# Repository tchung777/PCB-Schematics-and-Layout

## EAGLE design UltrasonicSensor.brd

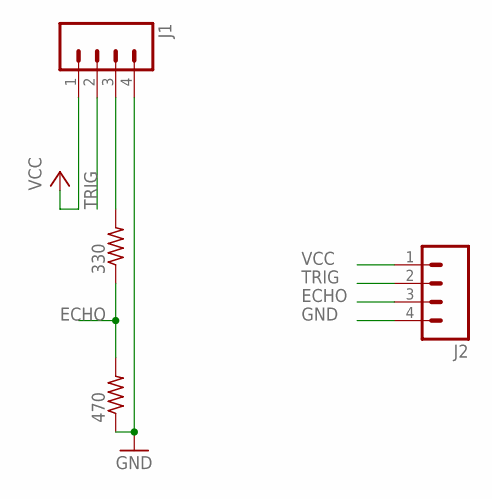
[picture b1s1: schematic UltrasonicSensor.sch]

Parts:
330, 470: R-US_0204/5; 0204/5
J1, J2: M04NO_SILK_ALL_ROUND; 1X04_NO_SILK_ALL_ROUND

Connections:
ECHO: 330.1, 470.2, J2.3
GND: 470.1, J1.4, J2.4
unnamed: 330.2, J1.3
TRIG: J1.2, J2.2
VCC: J1.1, J2.1

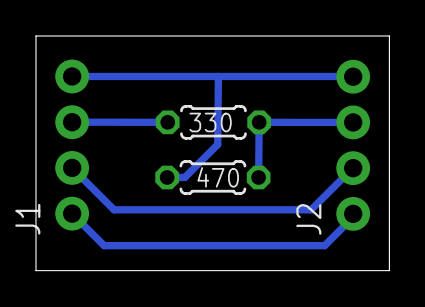
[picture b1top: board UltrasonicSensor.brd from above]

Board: 2 copper layers, 19.6 x 13.0 mm, 4 parts (0 on the bottom side), 5 nets.

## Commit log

2018-02-16 Implemented simple bus system for HC-SR04 Ultrasonic sensor.
2018-02-16 Added Bus System for Joystick and AD/DA converter that accompanies it. Move ultrasonic files to Ultrasonic folder.
2019-01-07 Fix image problem.

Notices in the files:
parts and their libraries:
SparkFun-Connectors: Licensing: Creative Commons ShareAlike 4.0 International - https://creativecommons.org/licenses/by-sa/4.0
